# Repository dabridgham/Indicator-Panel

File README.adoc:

= Indicator Panel

Here we replicate the functionality of DEC's indicator panels used on
PDP-11s and some other machines.  It was designed in conjunction with
the http://github.com/dabridgham/QSIC[QSIC project] to build a QBUS
board to emulate the old DEC disk drives using more modern storage
technology and we wanted to have blinkenlights to go with.

indicator-panel*:: KiCad design for the indicator panel circuit boards
   themselves.  Three boards make a full indicator panel.

adapter*:: A small adapter board to convert from the version 1 pinout
   to version 2.

inlay*:: Various inlay designs we've come up with to use with the
   QSIC.
   * inlay-qbus: QBUS monitor.
   * inlay-rk11-c: Our idea of what the RK11-C indicator panel might
     have looked like.
   * inlay-rk11-f: Used for both the RK11-F and the RP11-D, the new
      controllers we've created for the QSIC.
   * inlay-rp11: The RP11 indicator panel rendered here.
   * inlay-unibus: Unibus monitor.

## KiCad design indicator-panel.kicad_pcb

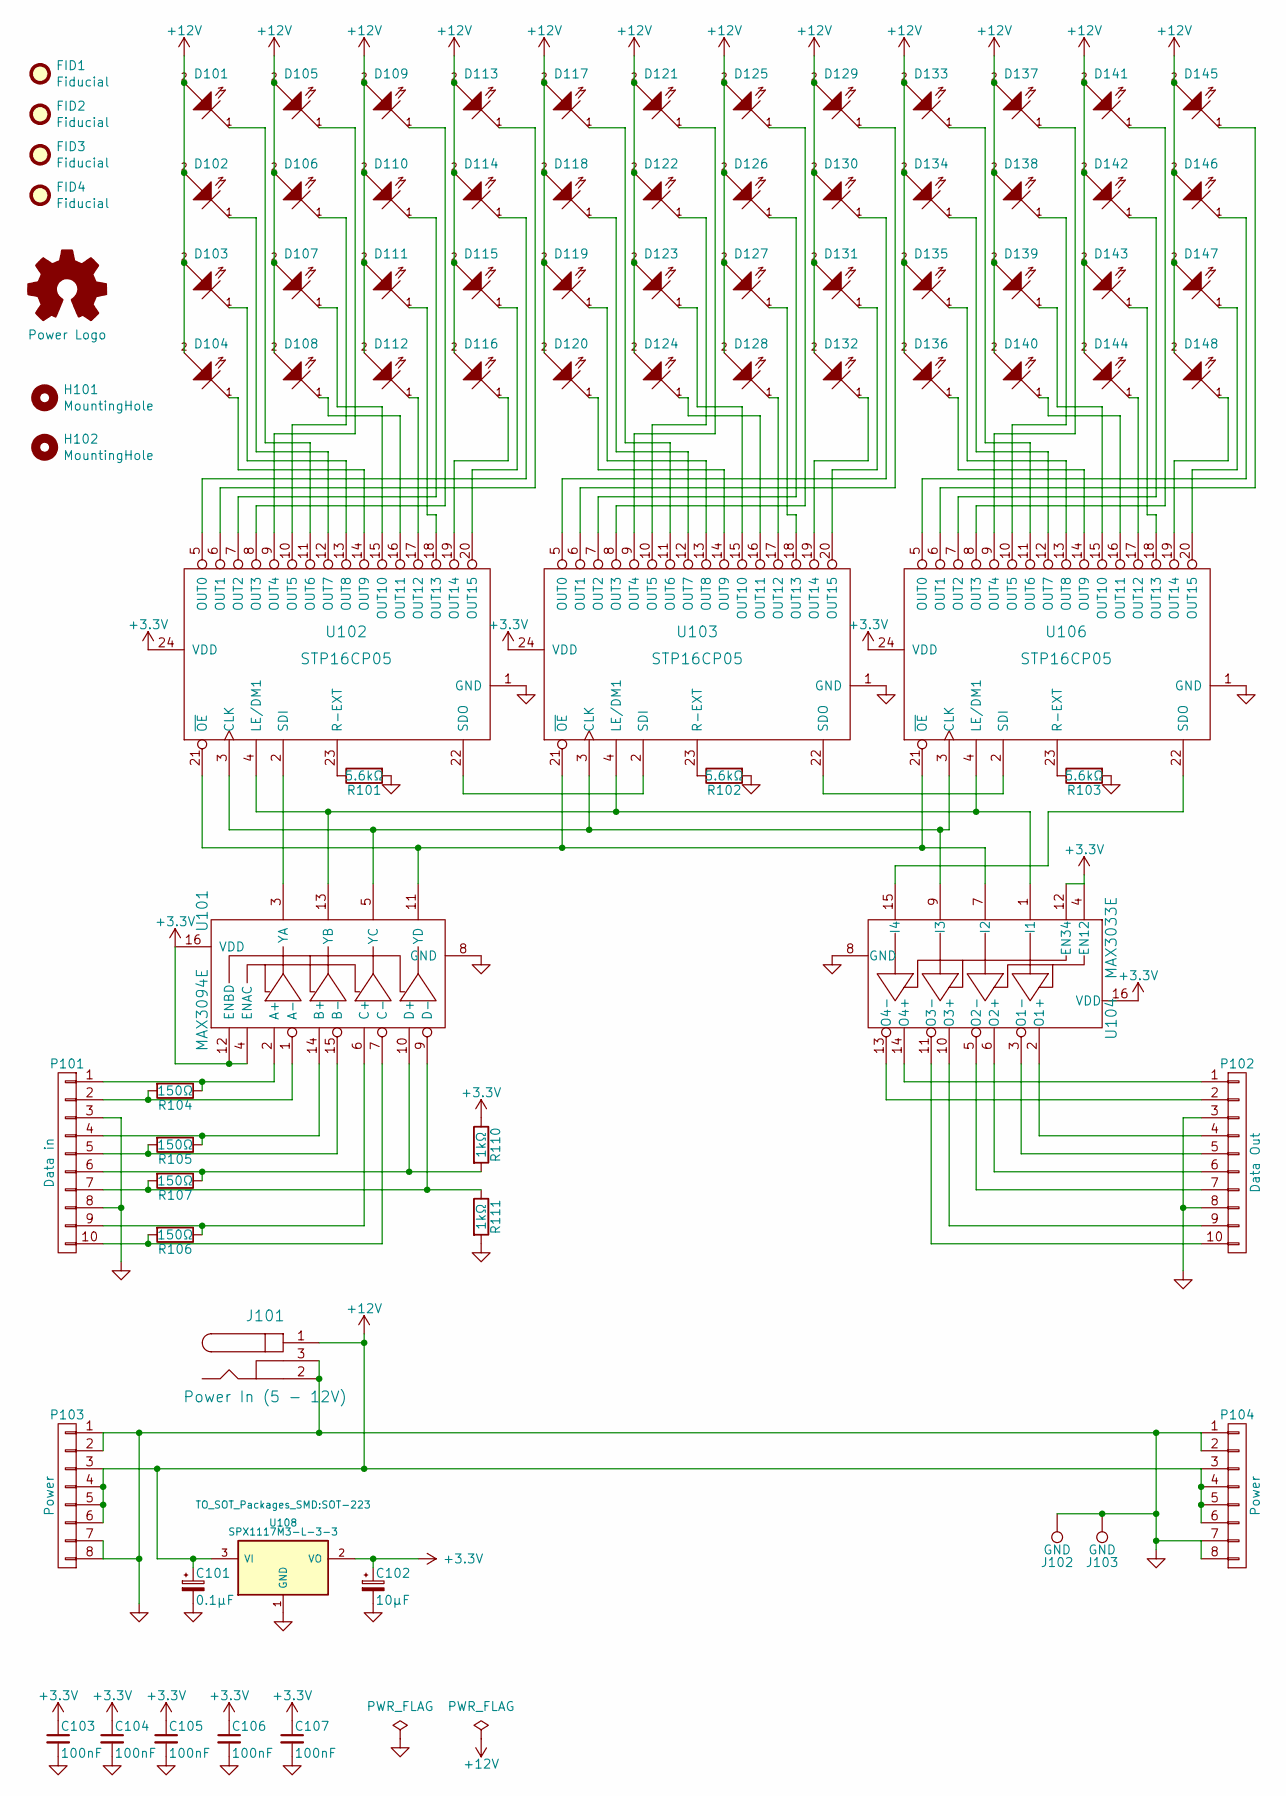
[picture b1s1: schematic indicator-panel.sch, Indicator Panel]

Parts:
C101: 0.1μF; CP_Tantalum_Case-R_EIA-2012-12_Reflow
C102: 10μF; CP_Tantalum_Case-R_EIA-2012-12_Wave
C103, C104, C105, C106, C107: 100nF; C_0805
D101, D102, D103, D104, D105, D106, D107, D108, D109, D110, D111, D112, D113, D114, D115, D116, D117, D118, D119, D120, D121, D122, D123, D124, D125, D126, D127, D128, D129, D130, D131, D132, D133, D134, D135, D136, D137, D138, D139, D140, D141, D142, D143, D144, D145, D146, D147, D148: LED-45; LED-0805
FID1, FID2, FID3, FID4: Fiducial; Fiducial_1mm_Mask2mm
H101, H102: MountingHole; MountingHole_3.5mm
J101: Power In (5 - 12V); PJ-032B
J102, J103: GND; MountingHole_3-5mm
P101: Data in; Pin_Header_Angled_2x05
P102: Data Out; Socket_Strip_Angled_2x05
P103: Power; Pin_Header_Angled_2x04
P104: Power; Socket_Strip_Angled_2x04
PowerLogo1: Power Logo; Barrel
R101, R102, R103: 5.6kΩ; R_0805
R104, R105, R106, R107: 150Ω; R_0805
R110, R111: 1kΩ; R_0805
U101: MAX3094E; SOIC-16_3.9x9.9mm_Pitch1.27mm
U102, U103, U106: STP16CP05; SOIC-24_7.5x15.4mm_Pitch1.27mm
U104: MAX3033E; SOIC-16_3.9x9.9mm_Pitch1.27mm
U108: SPX1117M3-L-3-3; SOT-223

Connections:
+3V3: C102.1, C103.1, C104.1, C105.1, C106.1, C107.1, R110.1, U101.4 (ENAC), U101.12 (ENBD), U101.16 (VDD), U102.24 (VDD), U103.24 (VDD), U104.4 (EN12), U104.12 (EN34), U104.16 (VDD), U106.24 (VDD), U108.2 (VO)
+12V: C101.1, D101.2 (A), D102.2 (A), D103.2 (A), D104.2 (A), D105.2 (A), D106.2 (A), D107.2 (A), D108.2 (A), D109.2 (A), D110.2 (A), D111.2 (A), D112.2 (A), D113.2 (A), D114.2 (A), D115.2 (A), D116.2 (A), D117.2 (A), D118.2 (A), D119.2 (A), D120.2 (A), D121.2 (A), D122.2 (A), D123.2 (A), D124.2 (A), D125.2 (A), D126.2 (A), D127.2 (A), D128.2 (A), D129.2 (A), D130.2 (A), D131.2 (A), D132.2 (A), D133.2 (A), D134.2 (A), D135.2 (A), D136.2 (A), D137.2 (A), D138.2 (A), D139.2 (A), D140.2 (A), D141.2 (A), D142.2 (A), D143.2 (A), D144.2 (A), D145.2 (A), D146.2 (A), D147.2 (A), D148.2 (A), J101.1, P103.3, P103.4, P103.5, P103.6, P104.3, P104.4, P104.5, P104.6, U108.3 (VI)
GND: C101.2, C102.2, C103.2, C104.2, C105.2, C106.2, C107.2, J101.2, J101.3, J102.1, J103.1, P101.3, P101.8, P102.3, P102.8, P103.1, P103.2, P103.7, P103.8, P104.1, P104.2, P104.7, P104.8, R101.2, R102.2, R103.2, R111.2, U101.8 (GND), U102.1 (GND), U103.1 (GND), U104.8 (GND), U106.1 (GND), U108.1 (GND)
unnamed: D101.1 (K), U102.11 (OUT6)
unnamed: D102.1 (K), U102.12 (OUT7)
unnamed: D103.1 (K), U102.13 (OUT8)
unnamed: D104.1 (K), U102.14 (OUT9)
unnamed: D105.1 (K), U102.9 (OUT4)
unnamed: D106.1 (K), U102.10 (OUT5)
unnamed: D107.1 (K), U102.15 (OUT10)
unnamed: D108.1 (K), U102.16 (OUT11)
unnamed: D109.1 (K), U102.8 (OUT3)
unnamed: D110.1 (K), U102.7 (OUT2)
unnamed: D111.1 (K), U102.18 (OUT13)
unnamed: D112.1 (K), U102.17 (OUT12)
unnamed: D113.1 (K), U102.6 (OUT1)
unnamed: D114.1 (K), U102.5 (OUT0)
unnamed: D115.1 (K), U102.20 (OUT15)
unnamed: D116.1 (K), U102.19 (OUT14)
unnamed: D117.1 (K), U103.11 (OUT6)
unnamed: D118.1 (K), U103.12 (OUT7)
unnamed: D119.1 (K), U103.13 (OUT8)
unnamed: D120.1 (K), U103.14 (OUT9)
unnamed: D121.1 (K), U103.9 (OUT4)
unnamed: D122.1 (K), U103.10 (OUT5)
unnamed: D123.1 (K), U103.15 (OUT10)
unnamed: D124.1 (K), U103.16 (OUT11)
unnamed: D125.1 (K), U103.8 (OUT3)
unnamed: D126.1 (K), U103.7 (OUT2)
unnamed: D127.1 (K), U103.18 (OUT13)
unnamed: D128.1 (K), U103.17 (OUT12)
unnamed: D129.1 (K), U103.6 (OUT1)
unnamed: D130.1 (K), U103.5 (OUT0)
unnamed: D131.1 (K), U103.20 (OUT15)
unnamed: D132.1 (K), U103.19 (OUT14)
unnamed: D133.1 (K), U106.11 (OUT6)
unnamed: D134.1 (K), U106.12 (OUT7)
unnamed: D135.1 (K), U106.13 (OUT8)
unnamed: D136.1 (K), U106.14 (OUT9)
unnamed: D137.1 (K), U106.9 (OUT4)
unnamed: D138.1 (K), U106.10 (OUT5)
unnamed: D139.1 (K), U106.15 (OUT10)
unnamed: D140.1 (K), U106.16 (OUT11)
unnamed: D141.1 (K), U106.8 (OUT3)
unnamed: D142.1 (K), U106.7 (OUT2)
unnamed: D143.1 (K), U106.18 (OUT13)
unnamed: D144.1 (K), U106.17 (OUT12)
unnamed: D145.1 (K), U106.6 (OUT1)
unnamed: D146.1 (K), U106.5 (OUT0)
unnamed: D147.1 (K), U106.20 (OUT15)
unnamed: D148.1 (K), U106.19 (OUT14)
unnamed: P101.1, R104.1, U101.2 (A+)
unnamed: P101.2, R104.2, U101.1 (A-)
unnamed: P101.4, R105.1, U101.14 (B+)
unnamed: P101.5, R105.2, U101.15 (B-)
unnamed: P101.6, R107.1, R110.2, U101.10 (D+)
unnamed: P101.7, R107.2, R111.1, U101.9 (D-)
unnamed: P101.9, R106.1, U101.6 (C+)
unnamed: P101.10, R106.2, U101.7 (C-)
unnamed: P102.1, U104.14 (O4+)
unnamed: P102.2, U104.13 (O4-)
unnamed: P102.4, U104.2 (O1+)
unnamed: P102.5, U104.3 (O1-)
unnamed: P102.6, U104.6 (O2+)
unnamed: P102.7, U104.5 (O2-)
unnamed: P102.9, U104.10 (O3+)
unnamed: P102.10, U104.11 (O3-)
unnamed: R101.1, U102.23 (R-EXT)
unnamed: R102.1, U103.23 (R-EXT)
unnamed: R103.1, U106.23 (R-EXT)
unnamed: U101.3 (YA), U102.2 (SDI)
unnamed: U101.5 (YC), U102.3 (CLK), U103.3 (CLK), U104.9 (I3), U106.3 (CLK)
unnamed: U101.11 (YD), U102.21 (~OE), U103.21 (~OE), U104.7 (I2), U106.21 (~OE)
unnamed: U101.13 (YB), U102.4 (LE/DM1), U103.4 (LE/DM1), U104.1 (I1), U106.4 (LE/DM1)
unnamed: U102.22 (SDO), U103.2 (SDI)
unnamed: U103.22 (SDO), U106.2 (SDI)
unnamed: U104.15 (I4), U106.22 (SDO)

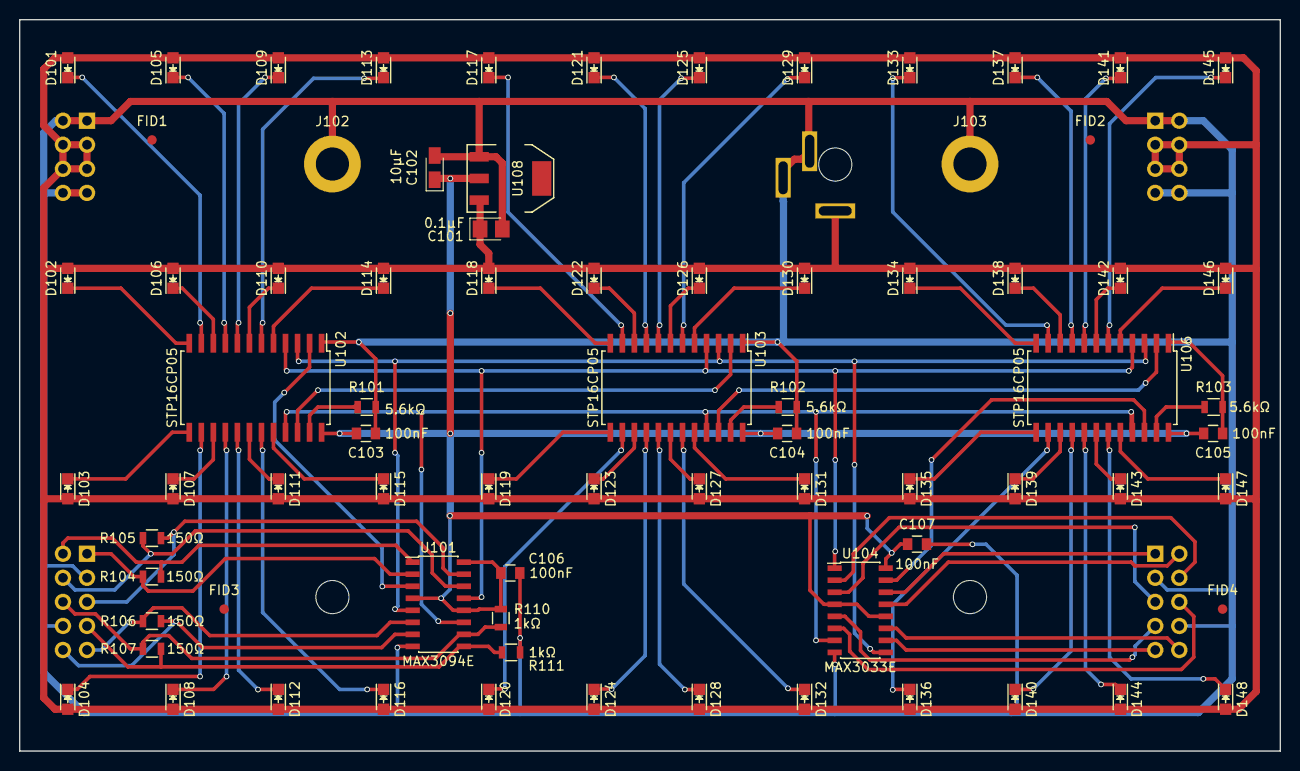
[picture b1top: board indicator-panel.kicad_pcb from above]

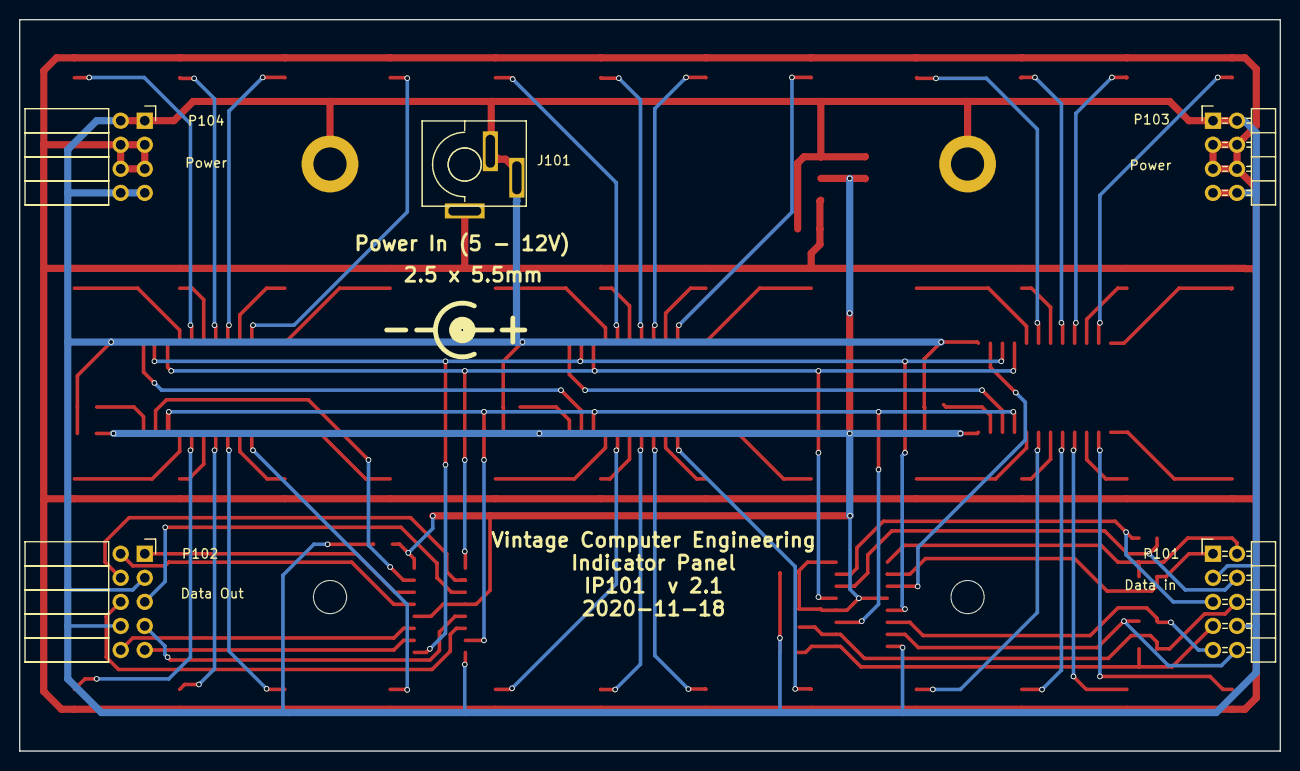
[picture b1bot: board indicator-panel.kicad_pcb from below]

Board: 2 copper layers, 133.1 x 77.2 mm, 84 parts (6 on the bottom side), 77 nets.

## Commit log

2015-10-12 Renamed lights to indicator-panel.
2015-10-12 Added the simple mechanical drawing for the indicator panel.
2015-10-14 Fix up connectors to carry current.
2015-10-27 Cleaned up schematic and added RK inlay.
2015-10-27 Overlays are really called inlays.
2015-10-28 Updated with more accurate dimensional information.
2015-11-11 Updated pcb and rk11 inlay to .44x.88 spacing.
2015-12-21 Changed data connector use so it can be reversed with no harm. Updated version to 1.1.
2016-01-14 Added barrel connector.
2016-02-20 Added barrel connector and shrunk schematic to Letter size. Last update before changing to add Blank and Board Detect signals.
2016-02-23 Changed to version 2.0 with the blanking signal and using a 4-unit rs485 receiver and transmitter.
2017-01-29 Monitor QBUS signals plus a little bit of QSIC status
2017-01-29 Updated current limiting resistor to 3.3k
2017-04-16 switched over to asciidoc
2017-11-23 Fix for correct spacing
2017-11-23 Line up connectors
2017-11-25 Updated to use correct spacing dimensions
2017-11-26 Moved mounting holes to give a better attach point in the light shield
2017-11-26 Swapped DAL and Latched Address. Re-worked the SD Card display to closer match what I'm doing in debugging the SD Card code.
2017-11-26 Make VDD and GND pins on chips visible.
2017-12-04 Relocated coaxial power connector and increased pad size on its footprint.
2017-12-11 Build pdf files from the inlay*.svg files.
2017-12-20 Added commands to make a poster
2017-12-26 Added fiducials and ground pads
2018-01-14 Changed current limiting resistor to 8.2k
2018-02-01 Added the rp11-d-2 poster
2018-02-01 Touch up some dates.
2018-02-26 Finalized v2 signal layout and submitted first batch for production.
2018-03-03 Initial README
2018-03-28 Added rk11-f poster
2018-03-28 Changed the tantalum capacitor footprint to more clearly show the positive end. Added some text around the power connector on the back.
2018-12-25 Adjusted fonts and sizes and spacing of inlays.
2019-01-07 Update README now that the Indicator Panel is its own project and add .gitignore.
2019-01-07 Updated now that the Indicator Panel is its own project.
2019-01-07 Bring in the cache and rescue files too.
2019-01-07 Add inlay-apr10 and put *.bak in .gitignore
2019-07-06 Rearranged for the micro-coded KV10
2020-02-25 Change one of the DMGO to DMGI. Reduce small letter spacing to 1 pixel.
2020-02-25 Added *.png
2020-02-25 Added inlay-unibus
2020-02-25 A first cut at a Unibus monitor panel
2021-12-04 Fix up the alignment and switch fonts. Also rename to rk11-c.
2021-12-04 Added inlay-rk11-c
2021-12-04 small tweaks
2021-12-04 Added fiducials
2022-10-15 Argument changes to inkscape
2022-10-15 Renamed inlay-rk11 to inlay-rk11-c and added inlay-unibus
2022-10-15 tweaks
2022-10-15 KiCAD changed the name of its .pro file.
